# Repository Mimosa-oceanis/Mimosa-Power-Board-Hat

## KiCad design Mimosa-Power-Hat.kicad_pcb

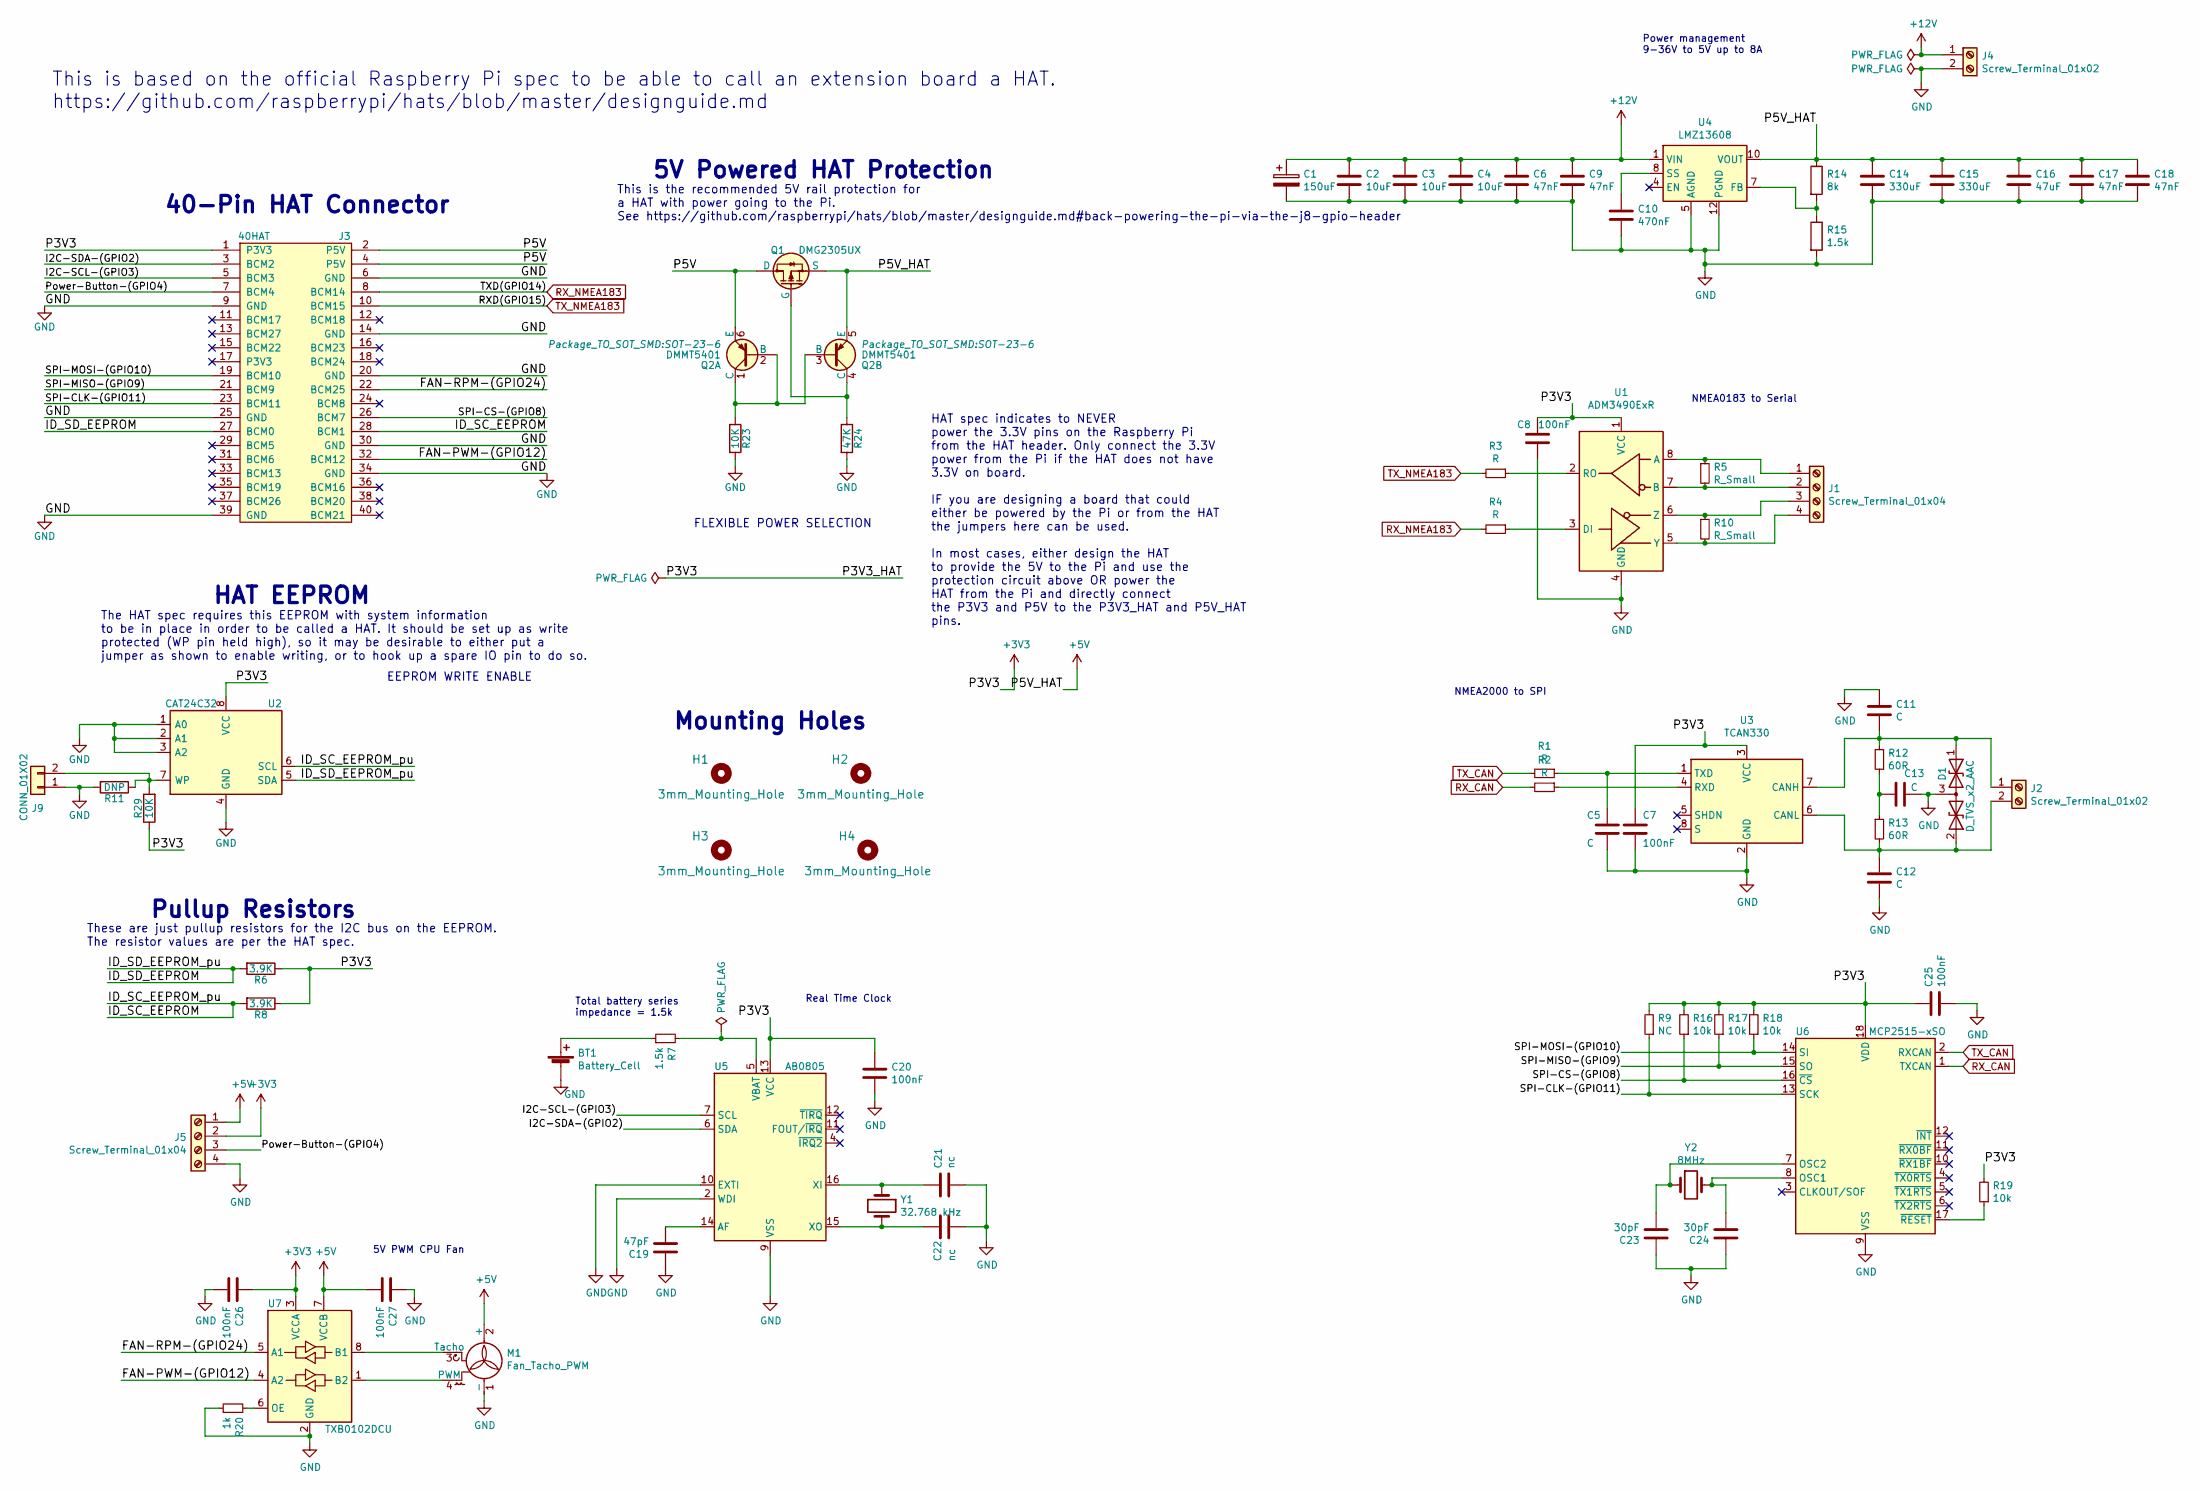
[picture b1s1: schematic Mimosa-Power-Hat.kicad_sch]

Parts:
BT1: Battery_Cell; BatteryHolder_Keystone_2998_1x6.8mm
C1: 150uF; CP_Elec_10x12.5
C2, C3, C4: 10uF; C_0805_2012Metric_Pad1.15x1.40mm_HandSolder
C5, C11, C12, C13: C; C_0805_2012Metric_Pad1.15x1.40mm_HandSolder
C6, C9, C17, C18: 47nF; C_0805_2012Metric_Pad1.15x1.40mm_HandSolder
C7, C8, C20, C25, C26, C27: 100nF; C_0805_2012Metric_Pad1.15x1.40mm_HandSolder
C10: 470nF; C_0805_2012Metric_Pad1.15x1.40mm_HandSolder
C14, C15: 330uF; CP_EIA-7343-31_Kemet-D_Pad2.25x2.55mm_HandSolder
C16: 47uF; C_0805_2012Metric_Pad1.15x1.40mm_HandSolder
C19: 47pF; C_0805_2012Metric_Pad1.15x1.40mm_HandSolder
C21, C22: nc; C_0805_2012Metric_Pad1.15x1.40mm_HandSolder
C23, C24: 30pF; C_0805_2012Metric_Pad1.15x1.40mm_HandSolder
D1: D_TVS_x2_AAC; SOT-23
H1, H2, H3, H4: 3mm_Mounting_Hole; NPTH_3mm_ID
J1, J5: Screw_Terminal_01x04; TerminalBlock_Phoenix_MKDS-3-4-5.08_1x04_P5.08mm_Horizontal
J2, J4: Screw_Terminal_01x02; TerminalBlock_Phoenix_MKDS-3-2-5.08_1x02_P5.08mm_Horizontal
J3: 40HAT; PinSocket_2x20_P2.54mm_Vertical
J9: CONN_01X02; PinHeader_1x02_P2.54mm_Vertical
M1: Fan_Tacho_PWM; FanPinHeader_1x04_P2.54mm_Vertical
Q1: DMG2305UX; SOT-23
Q2: DMMT5401; SOT-23-6
R1, R2, R3, R4: R; R_0805_2012Metric_Pad1.15x1.40mm_HandSolder
R5, R10: R_Small; R_0805_2012Metric_Pad1.15x1.40mm_HandSolder
R6, R8: 3.9K; R_0805_2012Metric_Pad1.15x1.40mm_HandSolder
R7, R15: 1.5k; R_0805_2012Metric_Pad1.15x1.40mm_HandSolder
R9: NC; R_0805_2012Metric_Pad1.15x1.40mm_HandSolder
R11: DNP; R_0805_2012Metric_Pad1.15x1.40mm_HandSolder
R12, R13: 60R; R_0805_2012Metric_Pad1.15x1.40mm_HandSolder
R14: 8k; R_0805_2012Metric_Pad1.15x1.40mm_HandSolder
R16, R17, R18, R19: 10k; R_0805_2012Metric_Pad1.15x1.40mm_HandSolder
R20: 1k; R_0805_2012Metric_Pad1.15x1.40mm_HandSolder
R23, R29: 10K; R_0805_2012Metric_Pad1.15x1.40mm_HandSolder
R24: 47K; R_0805_2012Metric_Pad1.15x1.40mm_HandSolder
U1: ADM3490ExR; SOIC-8_3.9x4.9mm_P1.27mm
U2: CAT24C32; SOIC-8_3.9x4.9mm_P1.27mm
U3: TCAN330; TSOT-23-8_HandSoldering
U4: LMZ13608; Texas_NDY0011A
U5: AB0805; VQFN-16-1EP_3x3mm_P0.5mm_EP1.8x1.8mm
U6: MCP2515-xSO; SOIC-18W_7.5x11.6mm_P1.27mm
U7: TXB0102DCU; VSSOP-8_2.4x2.1mm_P0.5mm
Y1: 32.768 kHz; Crystal_C26-LF_D2.1mm_L6.5mm_Horizontal
Y2: 8MHz; Crystal_SMD_Abracon_ABM3-2Pin_5.0x3.2mm_HandSoldering

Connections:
+3V3: C7.2, C8.1, C20.2, C25.2, C26.2, J3.1 (P3V3), J5.2, R6.1, R8.1, R9.2, R16.2, R17.2, R18.2, R19.2, R29.1, U1.1 (VCC), U2.8 (VCC), U3.3 (VCC), U5.13 (VCC), U6.18 (VDD), U7.3 (VCCA)
+5V: C14.1, C15.1, C16.1, C17.1, C18.1, C27.1, J5.1, M1.2 (+), Q1.2 (S), Q2.5 (E), R14.1, U4.10 (VOUT), U4.11 (VOUT), U7.7 (VCCB)
+12V: C1.1, C2.1, C3.1, C4.1, C6.1, C9.1, J4.1, U4.1 (VIN), U4.2 (VIN)
/FAN-PWM-(GPIO12): J3.32 (BCM12), U7.4 (A2)
/FAN-RPM-(GPIO24): J3.22 (BCM25), U7.5 (A1)
/I2C-SCL-(GPIO3): J3.5 (BCM3), U5.7 (SCL)
/I2C-SDA-(GPIO2): J3.3 (BCM2), U5.6 (SDA)
/ID_SC_EEPROM: J3.28 (BCM1), R8.2, U2.6 (SCL)
/ID_SD_EEPROM: J3.27 (BCM0), R6.2, U2.5 (SDA)
/P5V: J3.2 (P5V), J3.4 (P5V), Q1.3 (D), Q2.6 (E)
/Power-Button-(GPIO4): J3.7 (BCM4), J5.3
/SPI-CLK-(GPIO11): J3.23 (BCM11), R9.1, U6.13 (SCK)
/SPI-CS-(GPIO8): J3.26 (BCM7), R16.1, U6.16 (~CS)
/SPI-MISO-(GPIO9): J3.21 (BCM9), R17.1, U6.15 (SO)
/SPI-MOSI-(GPIO10): J3.19 (BCM10), R18.1, U6.14 (SI)
GND: BT1.2 (-), C1.2, C2.2, C3.2, C4.2, C5.1, C6.2, C7.1, C8.2, C9.2, C10.2, C11.2, C12.1, C13.1, C14.2, C15.2, C16.2, C17.2, C18.2, C19.2, C20.1, C21.1, C22.1, C23.2, C24.2, C25.1, C26.1, C27.2, D1.3 (common), J3.6 (GND), J3.9 (GND), J3.14 (GND), J3.20 (GND), J3.25 (GND), J3.30 (GND), J3.34 (GND), J3.39 (GND), J4.2, J5.4, J9.1, M1.1 (-), R11.2, R15.2, R20.1, R23.2, R24.2, U1.4 (GND), U2.1 (A0), U2.2 (A1), U2.3 (A2), U2.4 (GND), U3.2 (GND), U4.3 (AGND), U4.5 (AGND), U4.6 (AGND), U4.12 (PGND), U5.2 (WDI), U5.9 (VSS), U5.10 (EXTI), U5.17 (VSS), U6.9 (VSS), U7.2 (GND)
unnamed: BT1.1 (+), R7.1
unnamed: C5.2, R1.1, U3.1 (TXD)
unnamed: C10.1, U4.8 (SS)
unnamed: C11.1, D1.1 (A1), J2.1, R12.2, U3.7 (CANH)
unnamed: C12.2, D1.2 (A2), J2.2, R13.2, U3.6 (CANL)
unnamed: C13.2, R12.1, R13.1
unnamed: C19.1, U5.14 (AF)
unnamed: C21.2, U5.16 (XI), Y1.1
unnamed: C22.2, U5.15 (XO), Y1.2
unnamed: C23.1, U6.7 (OSC2), Y2.1
unnamed: C24.1, U6.8 (OSC1), Y2.2
unnamed: J1.1, R5.1, U1.8 (A)
unnamed: J1.2, R5.2, U1.7 (B)
unnamed: J1.3, R10.1, U1.6 (Z)
unnamed: J1.4, R10.2, U1.5 (Y)
unnamed: J9.2, R11.1, R29.2, U2.7 (WP)
unnamed: M1.3 (Tacho), U7.8 (B1)
unnamed: M1.4 (PWM), U7.1 (B2)
unnamed: Q1.1 (G), Q2.4 (C), R24.1
unnamed: Q2.1 (C), Q2.2 (B), Q2.3 (B), R23.1
unnamed: R2.1, U3.4 (RXD)
unnamed: R3.1, U1.2 (RO)
unnamed: R4.1, U1.3 (DI)
unnamed: R7.2, U5.5 (VBAT)
unnamed: R14.2, R15.1, U4.7 (FB)
unnamed: R19.1, U6.17 (~RESET)
unnamed: R20.2, U7.6 (OE)
RX_CAN: R2.2, U6.1 (TXCAN)
RX_NMEA183: J3.8 (BCM14), R4.2
TX_CAN: R1.2, U6.2 (RXCAN)
TX_NMEA183: J3.10 (BCM15), R3.2

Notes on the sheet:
This is based on the official Raspberry Pi spec to be able to call an extension board a HAT. https://github.com/raspberrypi/hats/blob/master/designguide.md
HAT spec indicates to NEVER power the 3.3V pins on the Raspberry Pi from the HAT header. Only connect the 3.3V power from the Pi if the HAT does not have 3.3V on board. IF you are designing a board that could either be powered by the Pi or from the HAT the jumpers here can be used. In most cases, e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
Real Time Clock
5V PWM CPU Fan
NMEA0183 to Serial
FLEXIBLE POWER SELECTION
This is the recommended 5V rail protection for a HAT with power going to the Pi. See https://github.com/raspberrypi/hats/blob/master/designguide.md#back-powering-the-pi-via-the-j8-gpio-header
Power management 9-36V to 5V up to 8A
Pullup Resistors
HAT EEPROM
EEPROM WRITE ENABLE
NMEA2000 to SPI
40-Pin HAT Connector
These are just pullup resistors for the I2C bus on the EEPROM. The resistor values are per the HAT spec.
The HAT spec requires this EEPROM with system information to be in place in order to be called a HAT. It should be set up as write protected (WP pin held high), so it may be desirable to either put a jumper as shown to enable writing, or to hook up a spare IO pin to do so.
Mounting Holes
5V Powered HAT Protection
Total battery series impedance = 1.5k

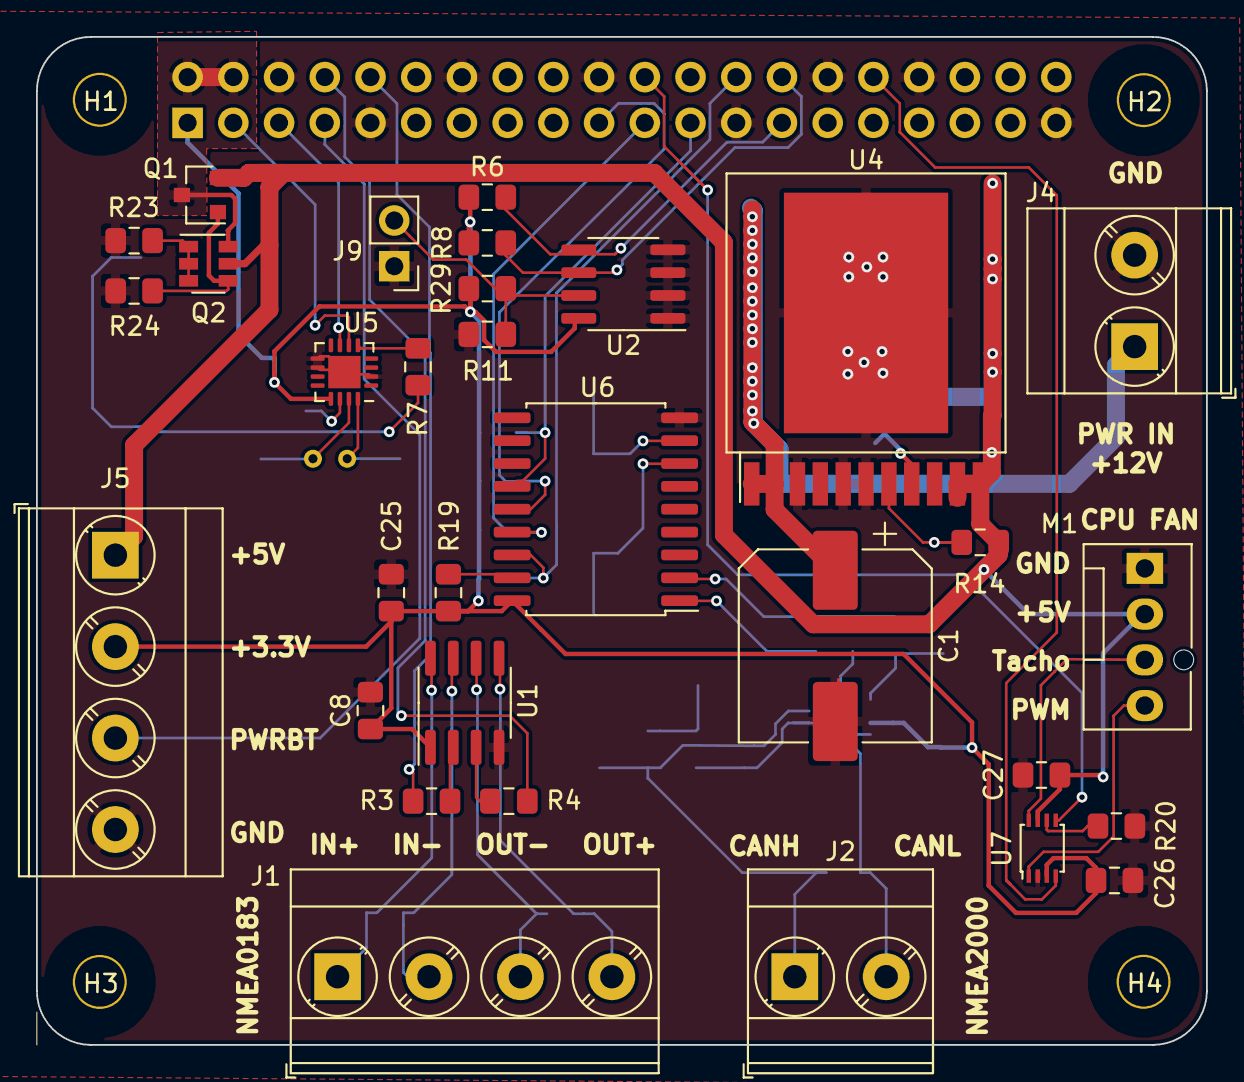
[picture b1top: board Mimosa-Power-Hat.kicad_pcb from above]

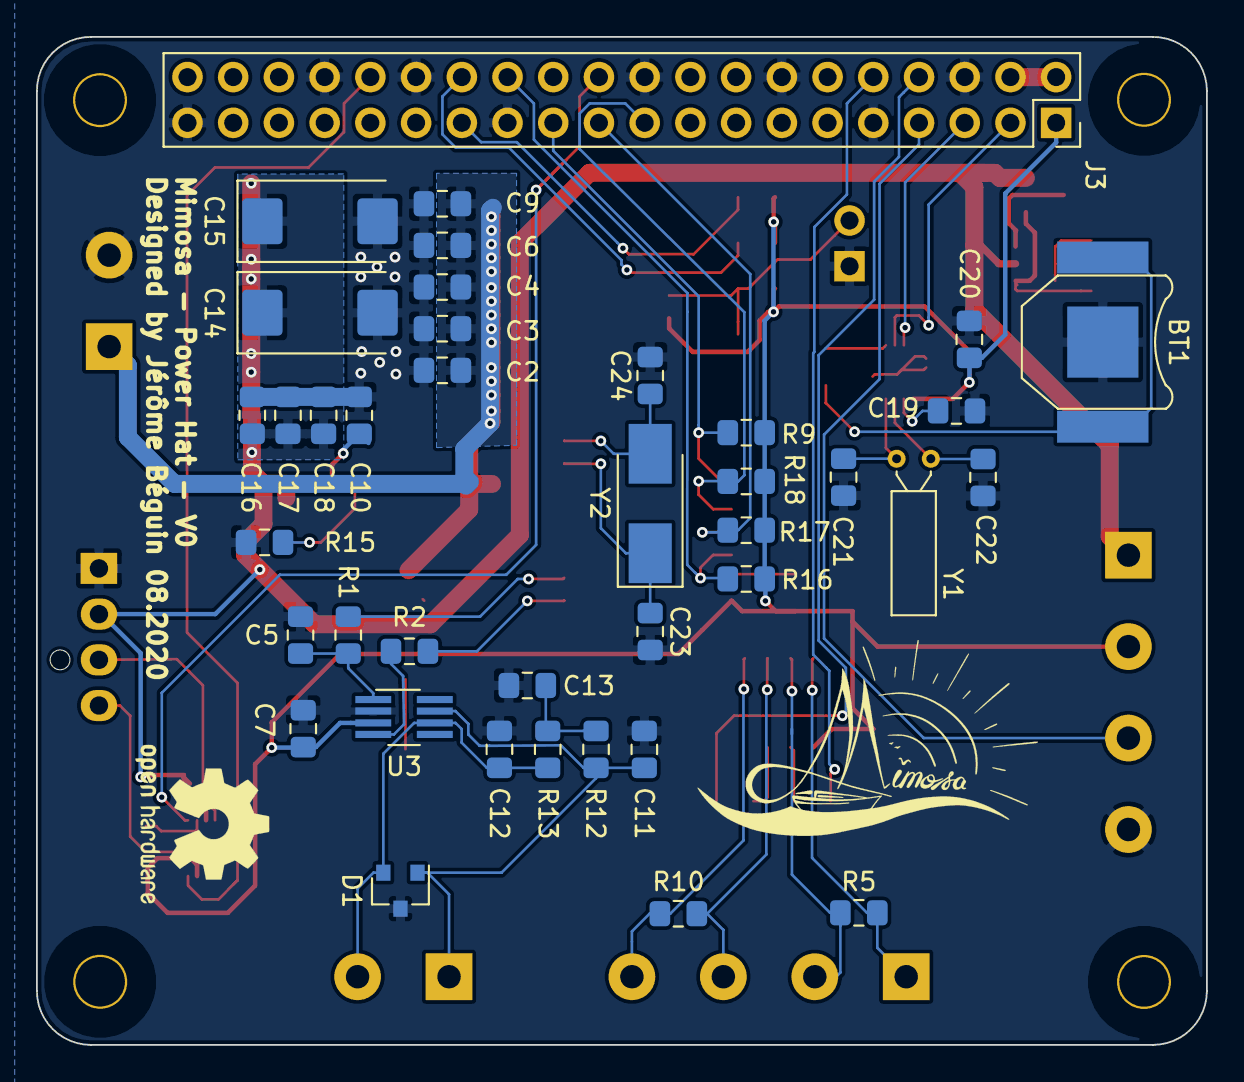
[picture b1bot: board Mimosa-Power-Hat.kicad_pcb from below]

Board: 2 copper layers, 65.0 x 56.0 mm, 74 parts (39 on the bottom side), 47 nets.

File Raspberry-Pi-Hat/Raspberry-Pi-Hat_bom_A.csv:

Component,Description,Part,References,Value,Footprint,Quantity Per PCB,Datasheet,Technologie,Fab,ESR,Ref
1,Single-cell battery,Battery_Cell,BT1,Battery_Cell,BatteryHolder_Keystone_2998_1x6.8mm,1,~,,,,
2,Unpolarized capacitor,C,C23 C24,30pF,C_0805_2012Metric_Pad1.15x1.40mm_HandSolder,2,~,,,,
3,Unpolarized capacitor,C,C19,47pF,C_0805_2012Metric_Pad1.15x1.40mm_HandSolder,1,~,,,,
4,Unpolarized capacitor,C,C6 C9 C17 C18,47nF,C_0805_2012Metric_Pad1.15x1.40mm_HandSolder,4,~,X7R ceramic X5R ceramic,,,
5,Unpolarized capacitor,C,C7 C8 C20 C25 C26 C27,100nF,C_0805_2012Metric_Pad1.15x1.40mm_HandSolder,6,~,,,,
6,Unpolarized capacitor,C,C10,470nF,C_0805_2012Metric_Pad1.15x1.40mm_HandSolder,1,~,,,,
7,Unpolarized capacitor,C,C2 C3 C4,10uF,C_0805_2012Metric_Pad1.15x1.40mm_HandSolder,3,~,X7R ceramic,,,
8,Unpolarized capacitor,C,C16,47uF,C_0805_2012Metric_Pad1.15x1.40mm_HandSolder,1,~,X5R ceramic,,,
9,Polarized capacitor,CP,C1,150uF,C_1206_3216Metric_Pad1.42x1.75mm_HandSolder,1,~,,,,
10,Unpolarized capacitor,C,C14 C15,330uF,CP_EIA-7343-31_Kemet-D_Pad2.25x2.55mm_HandSolder,2,~,Tantalum polymer,Kemet,15mR,T520D337M006ATE015
11,Unpolarized capacitor,C,C5 C11 C12 C13,C,C_0805_2012Metric_Pad1.15x1.40mm_HandSolder,4,~,,,,
12,Unpolarized capacitor,C,C21 C22,nc,C_0805_2012Metric_Pad1.15x1.40mm_HandSolder,2,~,,,,
13,"Bidirectional dual transient-voltage-suppression diode, center on pin 3",D_TVS_x2_AAC,D1,D_TVS_x2_AAC,SOT-23,1,~,,Nexperia,,PESD2ETH100-TR
14,,OX40HAT,J3,40HAT,PinSocket_2x20_P2.54mm_Vertical,1,,,,,
15,"Generic connector, single row, 01x02, script generated (kicad-library-utils/schlib/autogen/connector/)",Conn_01x02,J9,CONN_01X02,PinHeader_1x02_P2.54mm_Vertical,1,,,,,
16,"Generic screw terminal, single row, 01x02, script generated (kicad-library-utils/schlib/autogen/connector/)",Screw_Terminal_01x02,J2 J4,Screw_Terminal_01x02,TerminalBlock_Phoenix_MKDS-3-2-5.08_1x02_P5.08mm_Horizontal,2,~,,,,
17,"Generic screw terminal, single row, 01x04, script generated (kicad-library-utils/schlib/autogen/connector/)",Screw_Terminal_01x04,J1 J5,Screw_Terminal_01x04,TerminalBlock_Phoenix_MKDS-3-4-5.08_1x04_P5.08mm_Horizontal,2,~,,,,
18,"Fan, tacho output, PWM input, 4-pin connector",Fan_Tacho_PWM,M1,Fan_Tacho_PWM,FanPinHeader_1x04_P2.54mm_Vertical,1,http://www.formfactors.org/developer%5Cspecs%5Crev1_2_public.pdf,,,,
19,Transistor P-MOSFET,DMG2305UX,Q1,DMG2305UX,SOT-23,1,,,,,
20,PNP Matched Transistor Pair,DMMT5401,Q2,DMMT5401,SOT-23-6,1,,,,,
21,"Resistor, small symbol",R_Small,R12 R13,60R,R_0805_2012Metric_Pad1.15x1.40mm_HandSolder,2,~,,,,
22,"Resistor, small symbol",R_Small,R20,1k,R_0805_2012Metric_Pad1.15x1.40mm_HandSolder,1,~,,,,
23,Resistor,R,R15,1.5k,R_0805_2012Metric_Pad1.15x1.40mm_HandSolder,1,~,,,,
24,Resistor,R,R6 R8,3.9K,R_0805_2012Metric_Pad1.15x1.40mm_HandSolder,2,,,,,
25,Resistor,R,R14,8k,R_0805_2012Metric_Pad1.15x1.40mm_HandSolder,1,~,,,,
26,"Resistor, small symbol",R_Small,R16 R17 R18 R19 R23 R29,10k,R_0805_2012Metric_Pad1.15x1.40mm_HandSolder,6,~,,,,
27,Resistor,R,R24,47K,R_0805_2012Metric_Pad1.15x1.40mm_HandSolder,1,,,,,
28,"Resistor, small symbol",R_Small,R9,NC,R_0805_2012Metric_Pad1.15x1.40mm_HandSolder,1,~,,,,
29,"Resistor, small symbol",R_Small,R1 R2 R3 R4,R,R_0805_2012Metric_Pad1.15x1.40mm_HandSolder,4,~,,,,
30,"Resistor, small symbol",R_Small,R5 R10,R_Small,R_0805_2012Metric_Pad1.15x1.40mm_HandSolder,2,~,,,,
31,"Resistor, small symbol",R_Small,R7,TBD,R_0805_2012Metric_Pad1.15x1.40mm_HandSolder,1,~,,,,
32,"Real-Time Clock, I2C Interface, 3 GPO, QFN-16",AB0805,U5,AB0805,VQFN-16-1EP_3x3mm_P0.5mm_EP1.8x1.8mm,1,https://abracon.com/Precisiontiming/AB08X5-RTC.PDF,,,,
33,"RS-485, RS-422 full duplex 12 Mbps transceiver, SOIC-8",ADM3490ExR,U1,ADM3490ExR,SOIC-8_3.9x4.9mm_P1.27mm,1,https://www.analog.com/media/en/technical-documentation/data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,,,,
34,I2C Serial EEPROM 32Kb,CAT24C32,U2,CAT24C32,SOIC-8_3.9x4.9mm_P1.27mm,1,,,,,
35,"8A Adjustable Step-Down DC/DC Power Module in 15x15mm, Texas NDY0011A",LMZ13608,U4,LMZ13608,Texas_NDY0011A,1,http://www.ti.com/lit/ds/snvs710i/snvs710i.pdf,,,,
36,"Stand-Alone CAN Controller with SPI Interface, SOIC-18",MCP2515-xSO,U6,MCP2515-xSO,SOIC-18W_7.5x11.6mm_P1.27mm,1,http://ww1.microchip.com/downloads/en/DeviceDoc/21801e.pdf,,,,
37,"High-Speed CAN Transceiver, 1Mbps, 3.3V supply, silent mode, shutdown mode, SOT-23-8/SOIC-8",TCAN330,U3,TCAN330,TSOT-23-8_HandSoldering,1,http://www.ti.com/lit/ds/symlink/tcan337.pdf,,,,
38,2-Bit Bidirectional Voltage-Level Translator in VSSOP Package With Auto Direction Sensing and ±15-kV ESD Protection,TXB0102DCU,U7,TXB0102DCU,VSSOP-8_2.4x2.1mm_P0.5mm,1,http://www.ti.com/lit/ds/symlink/txb0102.pdf,,,,
39,Two pin crystal,Crystal,Y1,32.768 kHz,Crystal_C26-LF_D2.1mm_L6.5mm_Horizontal,1,~,,,,
40,Two pin crystal,Crystal,Y2,8MHz,Crystal_SMD_Abracon_ABM3-2Pin_5.0x3.2mm_HandSoldering,1,~,,,,





Component Groups:,41
Component Count:,70
Fitted Components:,69
Number of PCBs:,1
Total components:,69
Schematic Version:,A
Schematic Date:,
PCB Variant:,[u'default']
BoM Date:,"2020 August 11, Tuesday 16:20:13"
Schematic Source:,Raspberry-Pi-Hat.sch
KiCad Version:,Eeschema (5.1.5-0-10_14)

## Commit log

2020-05-24 Creation-of-the-file
    First save of the project.
2020-06-02 USB-UART
    Addition of USB-UART translator
2020-06-21 USB-HUB
    Implementation of USB HUB
2020-06-23 Starting placing component
    Assigned component footprint and started placing component on the board
2020-06-24 Placed all component on board
    All component placed on board.
    Not many space left. Will probably reduce size of capacitors and resistors.
2020-06-24 changed footprint size
    changed resistor and capacitor footprint size for 0603 when possible.
2020-06-25 Routted diff pair
    All USB lines is routed and most of the signal lines is routed as well.
2020-06-29 Change strategy
    Remove USB hub, connect CAN to SPI and NMEA to RSPI serial.
    Addition of RTC
    Addition of Fan PWM connector
    Plan to add a soft start button
2020-08-09 Routing version SPI V0
    Replaced USB with SPI for N2K
    Power button
    RTC
    Routing done
2020-08-11 All 3d model included
2020-08-14 Finalisation of the Project
    Correcte last problems
    Create gerber files
2020-08-14 adding BOM to prod folder
2020-08-15 Rename project and files and re-export prod files
2020-08-16 Add 3d Model
2020-08-16 reorganizing folder architerture
2020-08-16 creation of file prod zip for version 0
2020-11-03 Assembly documents
    adding Assembly files
2020-11-22 Adding testing protocol
2020-11-26 Creation of V1 - correction 1
    - Correction of battery holder who was not the proper size
    - Changed 12 to 5 DC regulator for a much cheaper one.
2020-12-10 Correction of silk postion of Q1 and Q2
2021-01-26 update on Linux
2021-02-18 Small update
2021-02-19 Correction of NMEA2000 RX/TX inversion, addition of seatalk circuit connection (not yet routed)
2021-04-04 add connection for seatalk, cleaned board and schematic
2022-01-08 update to Kicad 6
2022-02-08 New branch V2, update to kicad V6, Version of the board will add Attiny microcontroller for safe shutdown and watchdog.
2025-06-15 update project to last kicad version and cleaned the repo a bit
